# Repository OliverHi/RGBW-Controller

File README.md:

# Analog-RGBW-Controller
This is my rgbw controller project, where I am building a mysensors node to controll an analog RGBW led strip. 
The hardware is build around the arduino pro mini and NRF24L01+. 
The software is build on the MySensors project and is currently designed to work with Domoticz, Openhab 2 and homeAssistant (experimental) as a controller.

More infos can be found here: https://www.openhardware.io/view/74/MySensors-RGBW-Controller

## Project frozen/final
This project is done from my side. It has been working for years but I switched to another solution so I won't update this anymore. Feel free to send me Pull Requests though if you want anything updated or fork this repo.

If you are looking for a replacement follow me on [my blog](https://thesmarthomejourney.com/blog/) to see my current solution.

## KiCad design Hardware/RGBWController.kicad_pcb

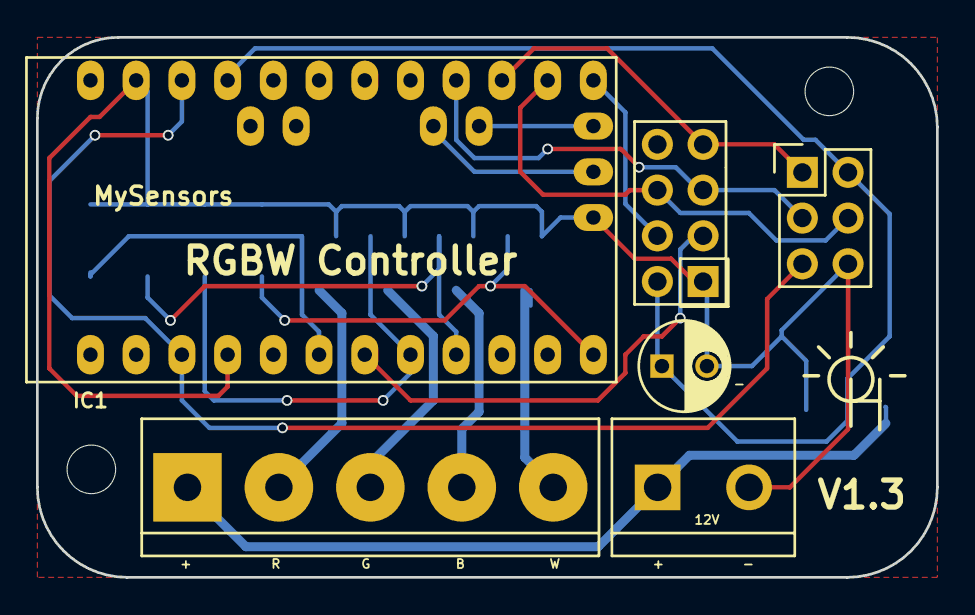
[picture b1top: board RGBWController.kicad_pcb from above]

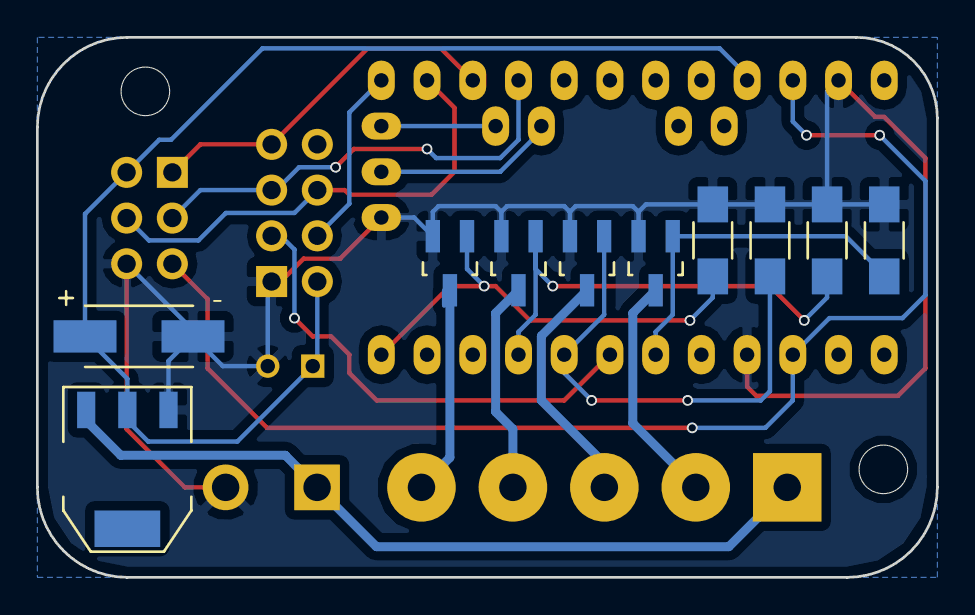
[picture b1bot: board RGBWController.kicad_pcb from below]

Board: 2 copper layers, 50.0 x 30.0 mm, 16 parts (10 on the bottom side), 17 nets.

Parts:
C1: CP; C_Radial_D5_L11_P2.5
C2: 22uF; TantalC_SizeC_EIA-6032_HandSoldering
CON1: AVR-ISP-6; Pin_Header_Straight_2x03
IC1: ArduinoProMini; pro_mini
P1: RGBW Strip; bornier5
P2: CONN_01X02; bornier2
Q1, Q2, Q3, Q4: IRLML2502; SOT-23_Handsoldering
R1, R2, R3, R4: R; R_1206_HandSoldering
U1: NRF24L01
U2: AMS1117; SOT-223

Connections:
+3V3: C1.1, C2.1, CON1.2, IC1.21, U1.2, U2.2
+12V: P1.1, P2.1, U2.3
B: IC1.9, Q3.1, R3.1
CE: IC1.7, U1.3
CSN: IC1.13, U1.4
G: IC1.8, Q2.1, R2.1
GND: C1.2, C2.2, CON1.6, IC1.4, IC1.23, IC1.29, P2.2, Q1.2, Q2.2, Q3.2, Q4.2, R1.2, R2.2, R3.2, R4.2, U1.1, U2.1
MISO: CON1.1, IC1.15, U1.7
MOSI: CON1.4, IC1.14, U1.6
unnamed: P1.2, Q1.3
unnamed: P1.3, Q2.3
unnamed: P1.4, Q3.3
unnamed: P1.5, Q4.3
R: IC1.6, Q1.1, R1.1
RST: CON1.5, IC1.3, IC1.22
SCK: CON1.3, IC1.16, U1.5
W: IC1.12, Q4.1, R4.1

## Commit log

2015-11-30 updated readme for the change from esp to mysensors/arduino
2015-11-30 added arduino sketch
2015-12-10 added PCB design + Gerber files
2016-03-12 updated sketch to use non linear fading and more compact code
2016-03-12 fixed some errors in the software
2016-03-13 changed dimming values to float
2016-04-02 small updates to datatypes in software
2016-04-02 added schema/pcb kicad files for the next version of the board
2016-05-01 added pictures for the PCB/Schematics
2016-05-01 moved software sketch
2016-05-01 added pictures of the build process
2016-05-08 added request for values to the software, experiments with dimming
2016-07-04 added on command on newcolor/dimming value, removed older version of code
2016-07-04 some more small software updates
2016-09-21 using set software name at presentation too
2016-09-22 changed initial values to only light up white but that one too 100%
2016-10-02 added nonlinear fading
2016-11-01 better update with new gerber files
2016-11-02 added all gerber exports, fixed gerber zip file
2016-11-13 updated sketch to mysensors 2
2017-08-01 updated sketch to support home assistant, added non-linear fading with set values
2017-08-09 code cleanup, homeassistant support now optional, initial fade up of the lights added
2017-08-09 updated readme with newer controller description
2017-08-11 fixed switched on/off log statements
2018-08-29 added stl files for the case
2019-04-20 Added project frozen/final message to readme
